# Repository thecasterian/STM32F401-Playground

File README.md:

STM32F401 Playground
====================

STM32F401 Breakout Board
------------------------

This is a breakout board for the STM32F401RCT6 microcontroller. It has a built-in ST-Link programmer just like ST's discovery boards. It also has a reset button, 8-MHz HSE crystal, and jumper pins for the BOOT0 and the virtual COM port.

References
----------

* [STM32F401 Reference Manual](https://www.st.com/resource/en/reference_manual/dm00096844-stm32f401xb-c-and-stm32f401xd-e-advanced-arm-based-32-bit-mcus-stmicroelectronics.pdf)
* [Custom ST-Link V2.0 / V2.1 / V3.0](https://hackaday.io/project/179054-custom-st-link-v20-v21-v30)
  * Reference for the hardware and the firmware of ST-Link programmer.

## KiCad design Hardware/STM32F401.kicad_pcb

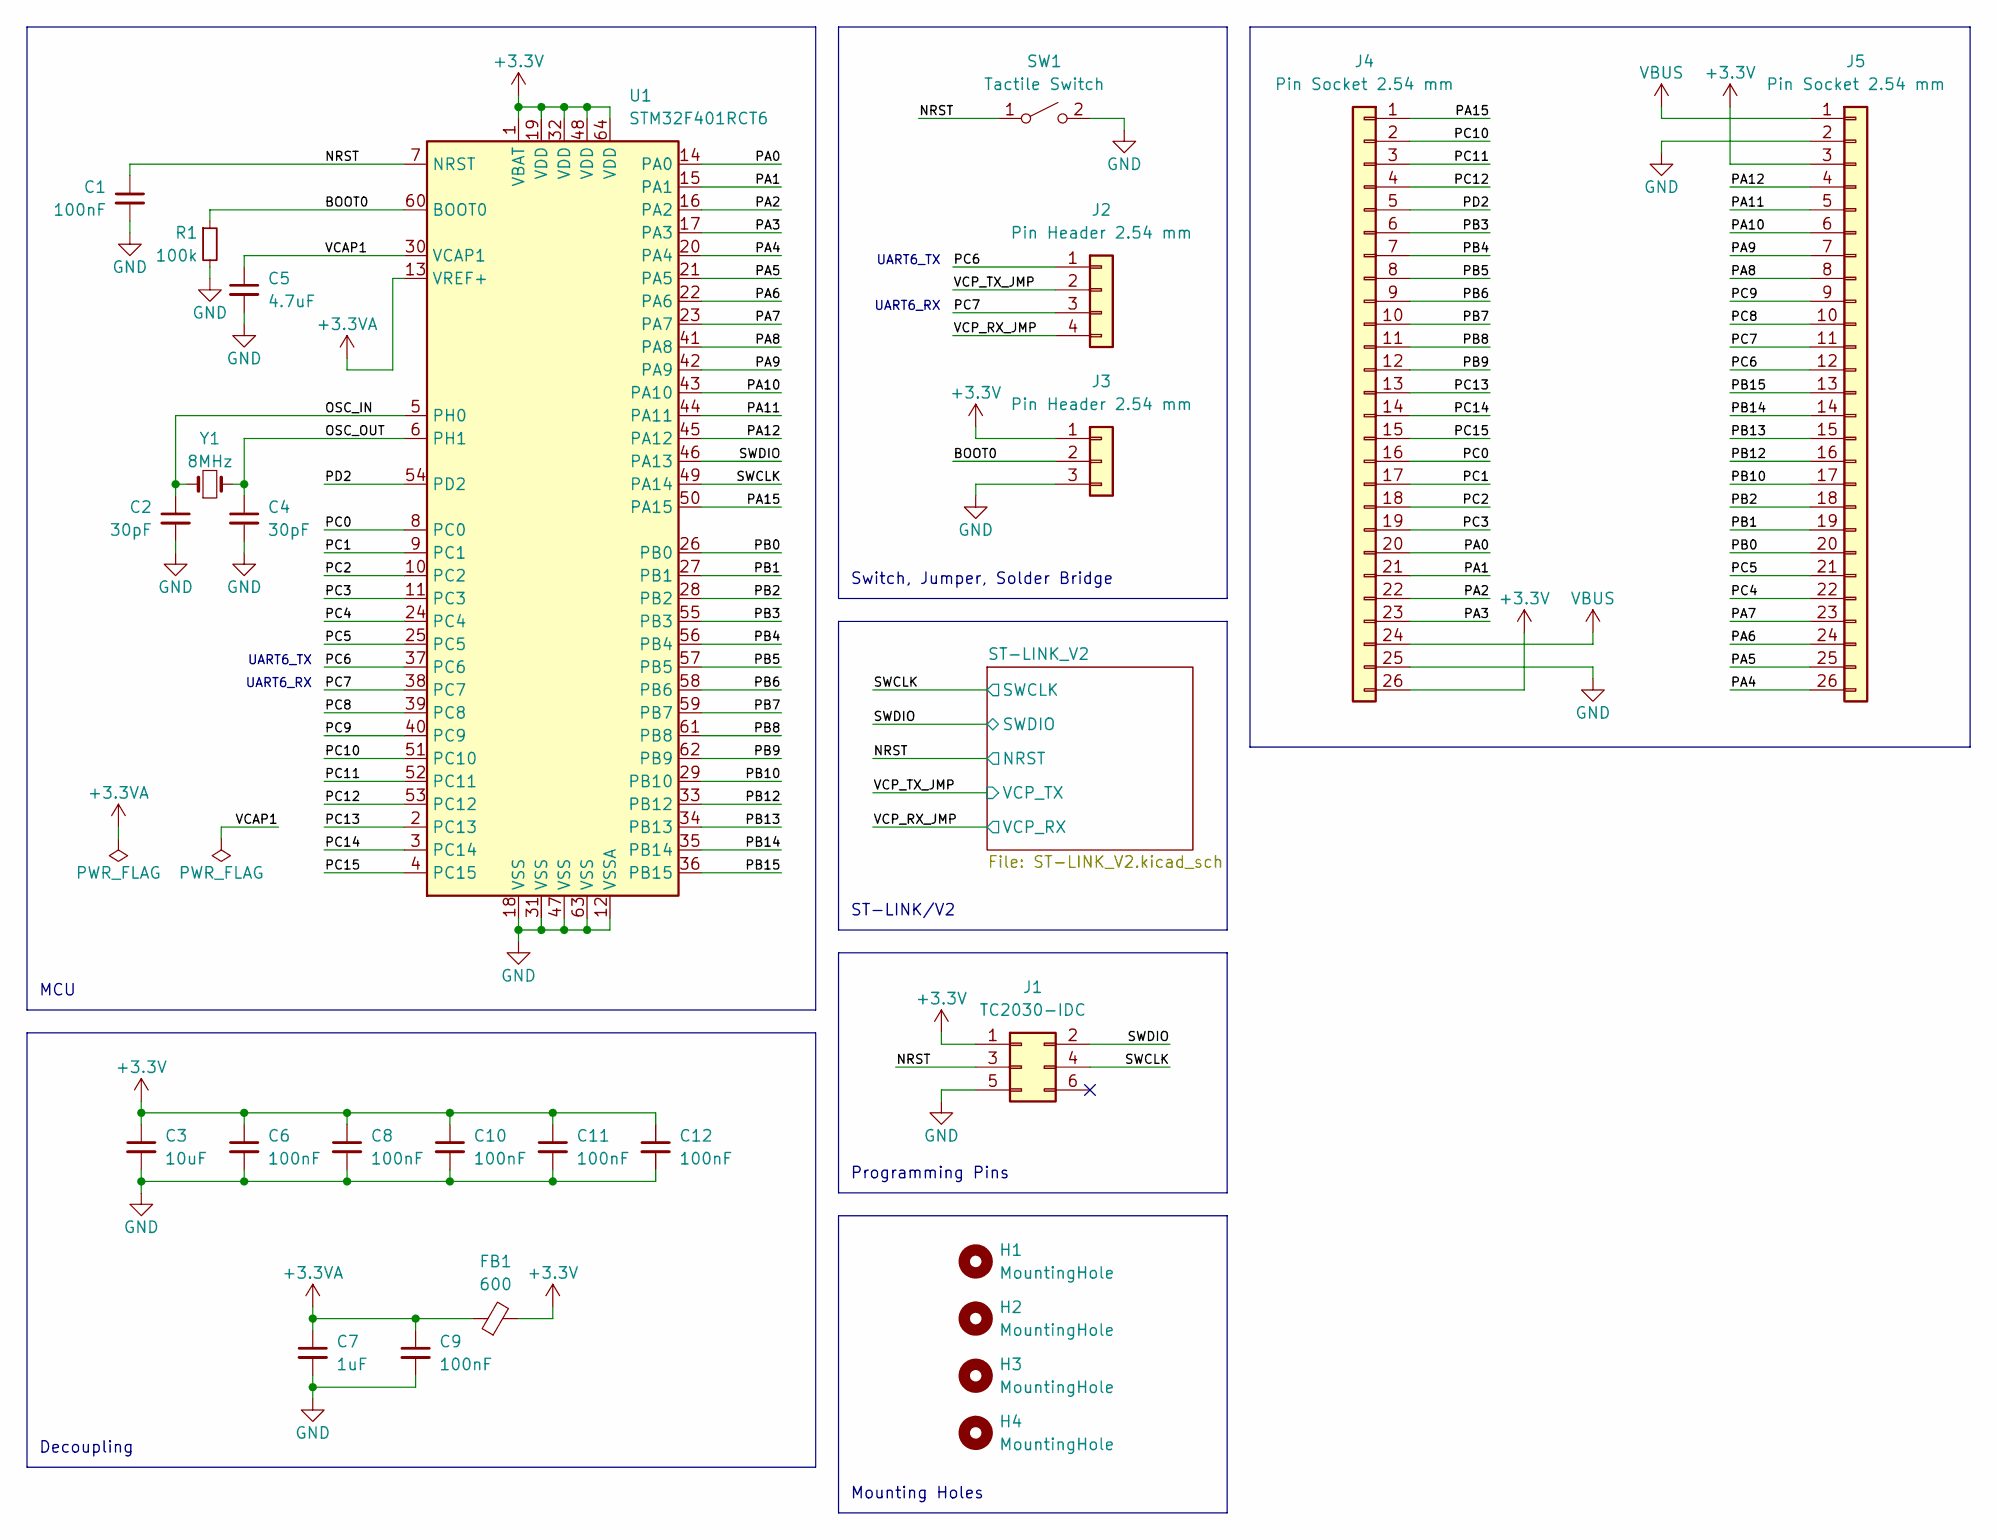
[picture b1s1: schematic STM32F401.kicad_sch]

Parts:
C1, C6, C8, C9, C10, C11, C12: 100nF; C_0603_1608Metric; LCSC C1525
C2, C4: 30pF; C_0603_1608Metric; LCSC C1570
C3: 10uF; C_0603_1608Metric; LCSC C19702
C5: 4.7uF; C_0603_1608Metric; LCSC C19666
C7: 1uF; C_0603_1608Metric; LCSC C15849
FB1: 600; L_0603_1608Metric; LCSC C1002
H1, H2, H3, H4: MountingHole; MountingHole_2.2mm_M2
J1: TC2030-IDC; Tag-Connect_TC2030-IDC-NL_2x03_P1.27mm_Vertical
J2: Pin Header 2.54 mm; PinHeader_1x04_P2.54mm_Vertical
J3: Pin Header 2.54 mm; PinHeader_1x03_P2.54mm_Vertical
J4, J5: Pin Socket 2.54 mm; PinSocket_1x26_P2.54mm_Vertical
R1: 100k; R_0603_1608Metric; LCSC C25741
SW1: Tactile Switch; SW_TS-1187A-B-A-B; LCSC C318884
U1: STM32F401RCT6; LQFP-64_10x10mm_P0.5mm; LCSC C74524
Y1: 8MHz; Crystal_SMD_5032-2Pin_5.0x3.2mm; LCSC C115962

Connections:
+3.3V: C3.1, C6.1, C8.1, C10.1, C11.1, C12.1, FB1.2, J1.1, J3.1, J4.26, J5.3, U1.1 (VBAT), U1.19 (VDD), U1.32 (VDD), U1.48 (VDD), U1.64 (VDD); also elsewhere on the board
+3.3VA: C7.1, C9.1, FB1.1, U1.13 (VREF+)
/BOOT0: J3.2, R1.1, U1.60 (BOOT0)
/NRST: C1.1, J1.3, SW1.1 (A), U1.7 (NRST); also elsewhere on the board
/OSC_IN: C2.1, U1.5 (PH0), Y1.1
/OSC_OUT: C4.1, U1.6 (PH1), Y1.2
/PA0: J4.20, U1.14 (PA0)
/PA1: J4.21, U1.15 (PA1)
/PA2: J4.22, U1.16 (PA2)
/PA3: J4.23, U1.17 (PA3)
/PA4: J5.26, U1.20 (PA4)
/PA5: J5.25, U1.21 (PA5)
/PA6: J5.24, U1.22 (PA6)
/PA7: J5.23, U1.23 (PA7)
/PA8: J5.8, U1.41 (PA8)
/PA9: J5.7, U1.42 (PA9)
/PA10: J5.6, U1.43 (PA10)
/PA11: J5.5, U1.44 (PA11)
/PA12: J5.4, U1.45 (PA12)
/PA15: J4.1, U1.50 (PA15)
/PB0: J5.20, U1.26 (PB0)
/PB1: J5.19, U1.27 (PB1)
/PB2: J5.18, U1.28 (PB2)
/PB3: J4.6, U1.55 (PB3)
/PB4: J4.7, U1.56 (PB4)
/PB5: J4.8, U1.57 (PB5)
/PB6: J4.9, U1.58 (PB6)
/PB7: J4.10, U1.59 (PB7)
/PB8: J4.11, U1.61 (PB8)
/PB9: J4.12, U1.62 (PB9)
/PB10: J5.17, U1.29 (PB10)
/PB12: J5.16, U1.33 (PB12)
/PB13: J5.15, U1.34 (PB13)
/PB14: J5.14, U1.35 (PB14)
/PB15: J5.13, U1.36 (PB15)
/PC0: J4.16, U1.8 (PC0)
/PC1: J4.17, U1.9 (PC1)
/PC2: J4.18, U1.10 (PC2)
/PC3: J4.19, U1.11 (PC3)
/PC4: J5.22, U1.24 (PC4)
/PC5: J5.21, U1.25 (PC5)
/PC6: J2.1, J5.12, U1.37 (PC6)
/PC7: J2.3, J5.11, U1.38 (PC7)
/PC8: J5.10, U1.39 (PC8)
/PC9: J5.9, U1.40 (PC9)
/PC10: J4.2, U1.51 (PC10)
/PC11: J4.3, U1.52 (PC11)
/PC12: J4.4, U1.53 (PC12)
/PC13: J4.13, U1.2 (PC13)
/PC14: J4.14, U1.3 (PC14)
/PC15: J4.15, U1.4 (PC15)
/PD2: J4.5, U1.54 (PD2)
/SWCLK: J1.4, U1.49 (PA14); also elsewhere on the board
/SWDIO: J1.2, U1.46 (PA13); also elsewhere on the board
/VCAP1: C5.1, U1.30 (VCAP1)
/VCP_RX_JMP: J2.4; also elsewhere on the board
/VCP_TX_JMP: J2.2; also elsewhere on the board
GND: C1.2, C2.2, C3.2, C4.2, C5.2, C6.2, C7.2, C8.2, C9.2, C10.2, C11.2, C12.2, J1.5, J3.3, J4.25, J5.2, R1.2, SW1.2 (B), U1.12 (VSSA), U1.18 (VSS), U1.31 (VSS), U1.47 (VSS), U1.63 (VSS); also elsewhere on the board
VBUS: J4.24, J5.1; also elsewhere on the board

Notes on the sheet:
Switch, Jumper, Solder Bridge
MCU
UART6_TX
Programming Pins
UART6_RX
ST-LINK/V2
Decoupling
Mounting Holes

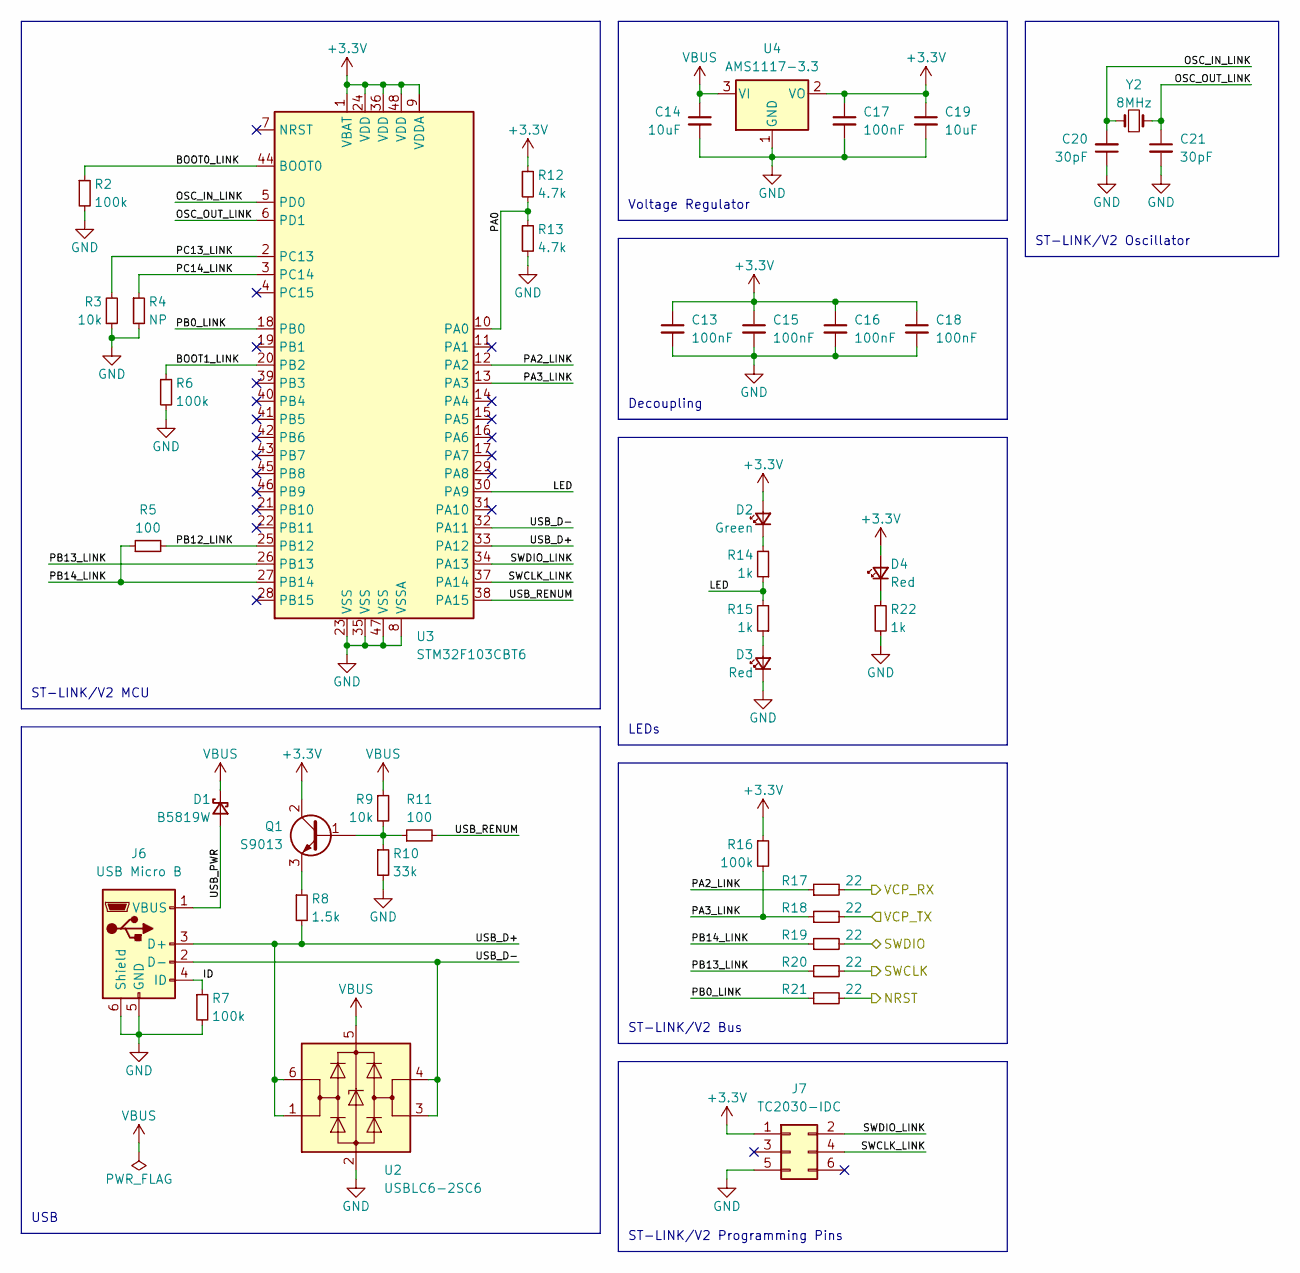
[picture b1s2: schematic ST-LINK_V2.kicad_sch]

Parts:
C13, C15, C16, C17, C18: 100nF; C_0603_1608Metric
C14, C19: 10uF; C_0603_1608Metric
C20, C21: 30pF; C_0603_1608Metric
D1: B5819W; D_SOD-123; LCSC C8598
D2: Green; LED_0603_1608Metric; LCSC C72043
D3, D4: Red; LED_0603_1608Metric; LCSC C2286
J6: USB Micro B; USB_Micro-B_Molex-105017-0001; LCSC C136000
J7: TC2030-IDC; Tag-Connect_TC2030-IDC-NL_2x03_P1.27mm_Vertical
Q1: S9013; SOT-23; LCSC C6749
R2, R6, R7, R16: 100k; R_0603_1608Metric
R3, R9: 10k; R_0603_1608Metric
R4: NP; R_0603_1608Metric
R5, R11: 100; R_0603_1608Metric
R8: 1.5k; R_0603_1608Metric
R10: 33k; R_0603_1608Metric
R12, R13: 4.7k; R_0603_1608Metric
R14, R15, R22: 1k; R_0603_1608Metric
R17, R18, R19, R20, R21: 22; R_0603_1608Metric
U2: USBLC6-2SC6; SOT-23-6
U3: STM32F103CBT6; LQFP-48_7x7mm_P0.5mm; LCSC C8304
U4: AMS1117-3.3; SOT-223-3_TabPin2; LCSC C6186
Y2: 8MHz; Crystal_SMD_5032-2Pin_5.0x3.2mm; LCSC C115962

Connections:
+3.3V: C13.1, C15.1, C16.1, C17.1, C18.1, C19.1, D2.2 (A), D4.2 (A), J7.1, Q1.2 (C), R12.1, R16.1, U3.1 (VBAT), U3.9 (VDDA), U3.24 (VDD), U3.36 (VDD), U3.48 (VDD), U4.2 (VO); also elsewhere on the board
/NRST: R21.2; also elsewhere on the board
/ST-LINK_V2/BOOT0_LINK: R2.1, U3.44 (BOOT0)
/ST-LINK_V2/BOOT1_LINK: R6.1, U3.20 (PB2)
/ST-LINK_V2/ID: J6.4 (ID), R7.1
/ST-LINK_V2/LED: R14.1, R15.2, U3.30 (PA9)
/ST-LINK_V2/OSC_IN_LINK: C20.2, U3.5 (PD0), Y2.1
/ST-LINK_V2/OSC_OUT_LINK: C21.1, U3.6 (PD1), Y2.2
/ST-LINK_V2/PA0: R12.2, R13.1, U3.10 (PA0)
/ST-LINK_V2/PA2_LINK: R17.1, U3.12 (PA2)
/ST-LINK_V2/PA3_LINK: R16.2, R18.1, U3.13 (PA3)
/ST-LINK_V2/PB0_LINK: R21.1, U3.18 (PB0)
/ST-LINK_V2/PB12_LINK: R5.2, U3.25 (PB12)
/ST-LINK_V2/PB13_LINK: R20.1, U3.26 (PB13)
/ST-LINK_V2/PB14_LINK: R5.1, R19.1, U3.27 (PB14)
/ST-LINK_V2/PC13_LINK: R3.2, U3.2 (PC13)
/ST-LINK_V2/PC14_LINK: R4.1, U3.3 (PC14)
/ST-LINK_V2/SWCLK_LINK: J7.4, U3.37 (PA14)
/ST-LINK_V2/SWDIO_LINK: J7.2, U3.34 (PA13)
/ST-LINK_V2/USB_D+: J6.3 (D+), R8.2, U2.1 (I/O1), U2.6 (I/O1), U3.33 (PA12)
/ST-LINK_V2/USB_D-: J6.2 (D-), U2.3 (I/O2), U2.4 (I/O2), U3.32 (PA11)
/ST-LINK_V2/USB_PWR: D1.2 (A), J6.1 (VBUS)
/ST-LINK_V2/USB_RENUM: R11.2, U3.38 (PA15)
/SWCLK: R20.2; also elsewhere on the board
/SWDIO: R19.2; also elsewhere on the board
/VCP_RX_JMP: R17.2; also elsewhere on the board
/VCP_TX_JMP: R18.2; also elsewhere on the board
GND: C13.2, C14.2, C15.2, C16.2, C17.2, C18.2, C19.2, C20.1, C21.2, D3.1 (K), J6.5 (GND), J6.6 (Shield), J7.5, R2.2, R3.1, R4.2, R6.2, R7.2, R10.2, R13.2, R22.2, U2.2 (GND), U3.8 (VSSA), U3.23 (VSS), U3.35 (VSS), U3.47 (VSS), U4.1 (GND); also elsewhere on the board
unnamed: D2.1 (K), R14.2
unnamed: D3.2 (A), R15.1
unnamed: D4.1 (K), R22.1
unnamed: Q1.1 (B), R9.2, R10.1, R11.1
unnamed: Q1.3 (E), R8.1
VBUS: C14.1, D1.1 (K), R9.1, U2.5 (VBUS), U4.3 (VI); also elsewhere on the board

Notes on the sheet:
Voltage Regulator
ST-LINK/V2 Programming Pins
USB
ST-LINK/V2 MCU
ST-LINK/V2 Bus
LEDs
Decoupling
ST-LINK/V2 Oscillator

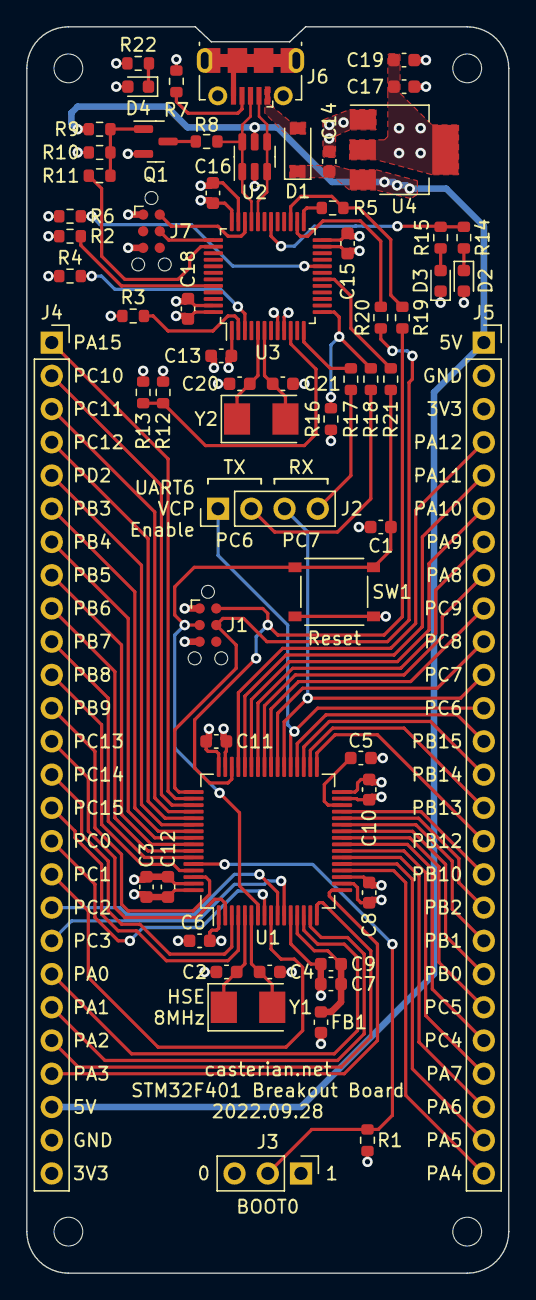
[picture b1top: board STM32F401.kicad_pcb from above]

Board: 4 copper layers, 36.8 x 95.2 mm, 67 parts (0 on the bottom side), 85 nets.

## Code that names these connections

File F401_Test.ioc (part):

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Mcu.Name=STM32F401R(B-C)Tx
Mcu.Package=LQFP64
Mcu.UserName=STM32F401RCTx
PA13.Mode=Serial_Wire
PA13.Signal=SYS_JTMS-SWDIO
PA14.Mode=Serial_Wire
PA14.Signal=SYS_JTCK-SWCLK
PA4.GPIOParameters=GPIO_Speed,PinState,GPIO_Label
PA4.GPIO_Label=W25Q128JV_NSS
PA4.GPIO_Speed=GPIO_SPEED_FREQ_VERY_HIGH
PA4.PinState=GPIO_PIN_SET
PA4.Signal=GPIO_Output
PA5.Mode=Full_Duplex_Master
PA5.Signal=SPI1_SCK
PA6.Mode=Full_Duplex_Master
PA6.Signal=SPI1_MISO
PA7.Mode=Full_Duplex_Master
PA7.Signal=SPI1_MOSI
PB10.Mode=Full_Duplex_Master
PB10.Signal=SPI2_SCK
PC1.GPIOParameters=GPIO_Label,GPIO_Speed,PinState
PC1.GPIO_Label=MPU9250_NSS
PC1.GPIO_Speed=GPIO_SPEED_FREQ_VERY_HIGH
PC1.PinState=GPIO_PIN_SET
PC1.Signal=GPIO_Output
PC2.Mode=Full_Duplex_Master
PC2.Signal=SPI2_MISO
PC3.Mode=Full_Duplex_Master
PC3.Signal=SPI2_MOSI
PC6.Mode=Asynchronous
PC6.Signal=USART6_TX
PC7.Mode=Asynchronous
PC7.Signal=USART6_RX
PH0\ -\ OSC_IN.Mode=HSE-External-Oscillator
PH0\ -\ OSC_IN.Signal=RCC_OSC_IN
PH1\ -\ OSC_OUT.Mode=HSE-External-Oscillator
PH1\ -\ OSC_OUT.Signal=RCC_OSC_OUT
RCC.HSE_VALUE=8000000
RCC.SYSCLKFreq_VALUE=84000000
RCC.SYSCLKSource=RCC_SYSCLKSOURCE_PLLCLK
board=custom

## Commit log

2022-10-23 Add basic codes
2022-10-23 Implement W25Q128JV flash driver
2022-10-28 Implement MPU9250 accelerometer and gyro interface
2022-11-04 Implement AHRS with only gyro
2022-11-05 Add accelerometer to AHRS
2022-11-05 Implement magnetometer interface
2022-11-07 Add magnetometer to AHRS
2022-11-13 Fix bug on quaternion calculation
2023-01-10 Add hardware
2023-01-10 Add readme
